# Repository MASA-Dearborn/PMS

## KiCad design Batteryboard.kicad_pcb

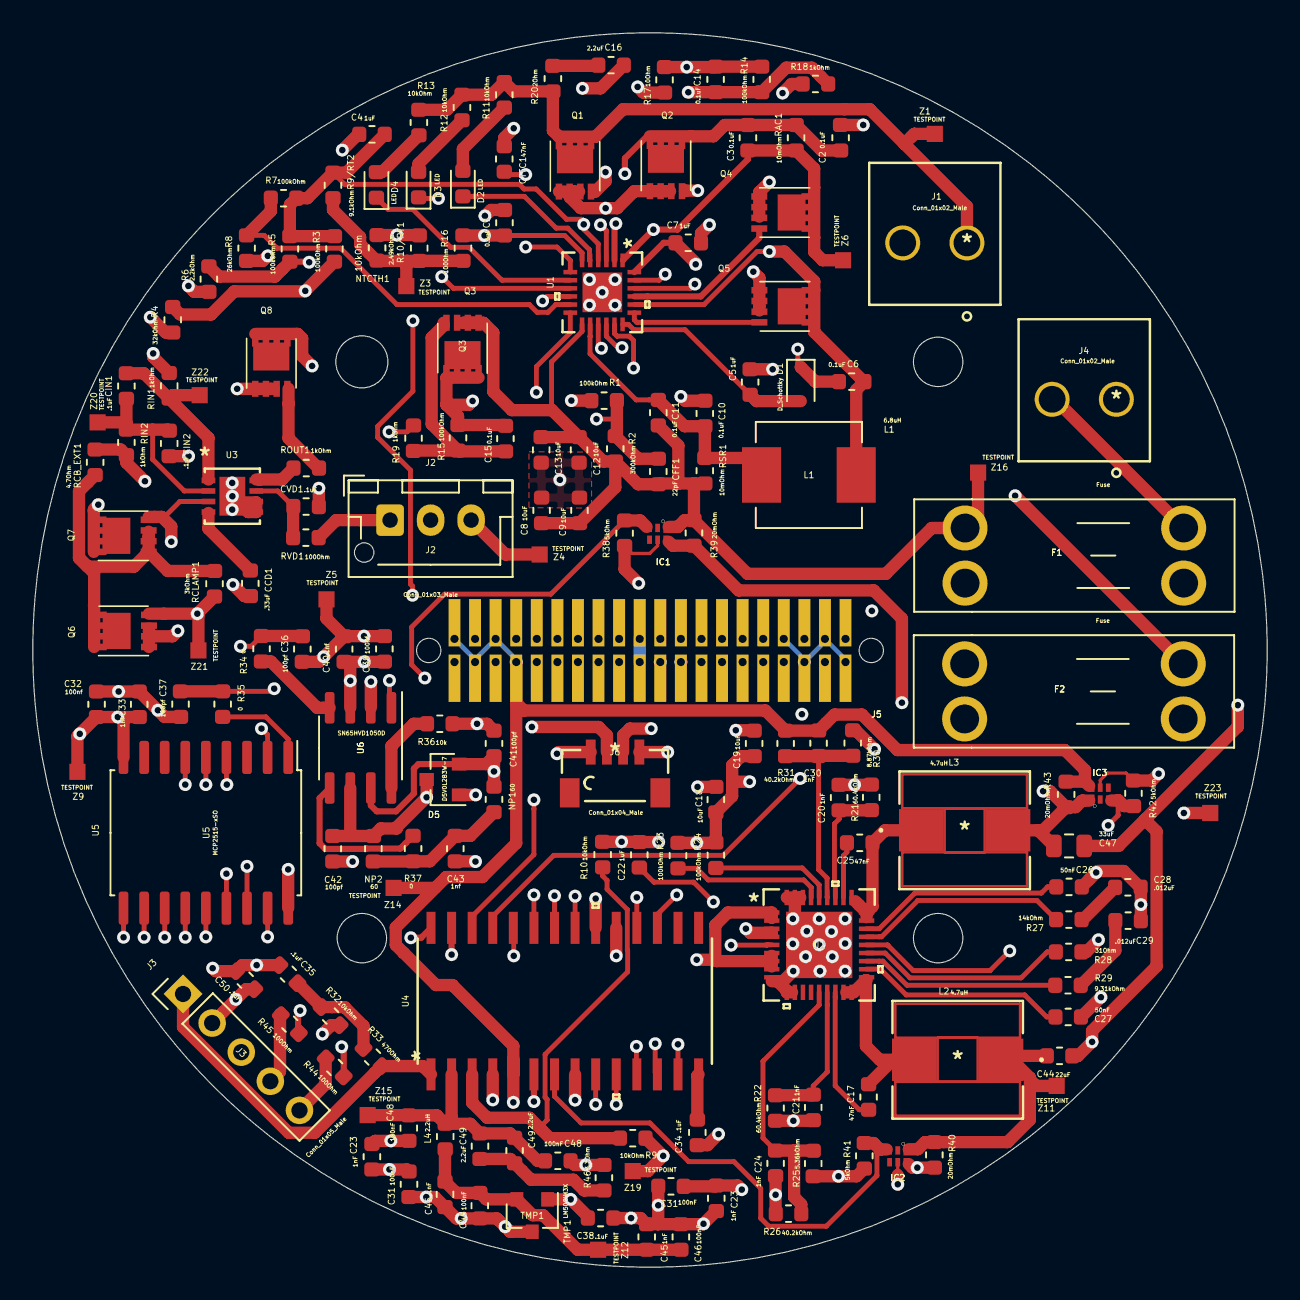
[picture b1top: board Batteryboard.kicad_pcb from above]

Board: 4 copper layers, 76.2 x 76.2 mm, 173 parts (1 on the bottom side), 102 nets.

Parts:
C1, C2, C3, C6, C10, C11, C14, C15: 0.1uF; C_0603_1608Metric
C4, C5, C7, C22: 1uF; C_0603_1608Metric
C8, C9, C12, C13, C18, C19: 10uF; C_0603_1608Metric
C16, C49, C49#2: 2.2uF; C_0603_1608Metric
C17, C25: 47nF; C_0603_1608Metric
C20, C21, C23, C23#2, C24, C30, C45, C45#2: 1nF; C_0603_1608Metric
C26, C27: 50nF; C_0603_1608Metric
C28, C29: .012uF; C_0603_1608Metric
C31, C31#2, C46, C46#2, C48, C48#2: 100nF; C_0603_1608Metric
C32, C40: 100nf; C_0603_1608Metric
C33, C39, C43: 1nf; C_0603_1608Metric
C34, C35, C38, C50: .1uF; C_0603_1608Metric
C36, C37, C41, C42: 100pf; C_0603_1608Metric
C44: 22uF; C_0603_1608Metric
C47: 33uF; C_0805_2012Metric
CCD1: .33uF; C_0603_1608Metric
CFF1: 22pF; C_0603_1608Metric
CIN1, CIN2: .1uF; C_0603_1608Metric
CTTC1: 47nF; C_0603_1608Metric
CVD1: .1uF; C_0603_1608Metric
D1: D_Schottky; D_SOD-323
D2, D3, D4: LED; D_0603_1608Metric
D5: D5V0L2B3W-7; SOT-23
F1, F2: Fuse; Fuseholder_Blade_Mini_Keystone_3557-2
IC1, IC2, IC3: FAN4010IL6X_F113; 6-LEAD_MICROPAK
J1, J4: Conn_01x02_Male; 1-1123723-2
J2: Conn_01x03_Male; JST_XH_B3B-XH-AM_1x03_P2.50mm_Vertical
J3: Conn_01x05_Male; PinHeader_1x05_P2.54mm_Vertical
J5: SC_19-20; bottom_Stack_Connector_2019_2020
J6: Conn_01x04_Male; 1734595-4
L1: 6.8uH; L_Vishay_IHLP-2525
L2, L3: 4.7uH; SRP7030-4R7M
L4: 2.2uH; L_0603_1608Metric
NP1, NP2: 60; R_0603_1608Metric
NTCTH1: 10kOhm; R_0603_1608Metric
Q1, Q2, Q3, Q7: SI7617DN-T1-GE3; SIS862DNT1GE3
Q4, Q5, Q6, Q8: SIS412DN-T1-GE3; SIS862DNT1GE3
R1, R3, R5, R7, R14, R15, R23, R24: 100kOhm; R_0603_1608Metric
R2: 300kOhm; R_0603_1608Metric
R4: 32kOhm; R_0603_1608Metric
R6: 2.2kOhm; R_0603_1608Metric
R8: 26kOhm; R_0603_1608Metric
R9, R10, R11, R12, R13, R32: 10kOhm; R_0603_1608Metric
R9/RT2: 9.1kOhm; R_0603_1608Metric
R10/RT1: 2.49kOhm; R_0603_1608Metric
R16, R44, R45: 100Ohm; R_0603_1608Metric
R17: 10Ohm; R_0603_1608Metric
R18, R19: 1kOhm; R_0603_1608Metric
R20: 2Ohm; R_0603_1608Metric
R21, R22: 60.4kOhm; R_0603_1608Metric
R25: 5.36kOhm; R_0603_1608Metric
R26, R31: 40.2kOhm; R_0603_1608Metric
R27: 14kOhm; R_0603_1608Metric
R28: 31Ohm; R_0603_1608Metric
R29: 9.31kOhm; R_0603_1608Metric
R30: 8.87kOhm; R_0603_1608Metric
R33: 470Ohm; R_0603_1608Metric
R34, R35, R37: 0; R_0603_1608Metric
R36: 10k; R_0603_1608Metric
R38, R41, R42: 5kOhm; R_0603_1608Metric
R39, R40, R43: 20mOhm; R_0603_1608Metric
R46: 3.3Ohm; R_0603_1608Metric
RAC1: 10mOhm; R_0603_1608Metric
RCB_EXT1: 4.7Ohm; R_0603_1608Metric
RCLAMP1: 3kOhm; R_0603_1608Metric
RIN1, RIN2: 1kOhm; R_0603_1608Metric
ROUT1: 1kOhm; R_0603_1608Metric
RSR1: 10mOhm; R_0603_1608Metric
RVD1: 100Ohm; R_0603_1608Metric
R_JUMP1: 0Ohm; R_0603_1608Metric
TMP1: LM50CIM3X; SOT-23
U1: BQ24617RGET
U2: TPS65279DAPR
U3: BQ29200DRBT
U4: PIC18F25K50-I_SO; PIC18F25K50-I&slash_SO
U5: MCP2515-xSO; SOIC-18W_7.5x11.6mm_P1.27mm
U6: SN65HVD1050D; SOIC-8_3.9x4.9mm_P1.27mm
Z1, Z3, Z4, Z5, Z6, Z9, Z11, Z12, Z14, Z15, Z16, Z19, Z20, Z21, Z22, Z23: TESTPOINT

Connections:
3V3: C30.2, C50.1, IC3.6, J3.2, J5.2, J5.3, J5.6, J5.7, R31.2, R43.1, U4.5, Z14.1
3V3CURRENT: IC3.3, R42.1, U4.25
5V0: C23.1, C23#2.1, C24.2, C31.2, C31#2.2, C32.1, C33.2, C38.1, C39.2, C40.1, IC2.6, J5.34, J5.35, J5.38, J5.39, J6.1, R26.2, R32.1, R40.2, TMP1.1, U4.4, U4.20, U5.9, U6.3, Z9.1
5VCURRENT: IC2.3, R41.1, U4.7
ACSET: R3.2, R4.1, U1.16
BTST: C6.2, D1.1, U1.22
CAN_H: C41.2, D5.2, J5.21, J6.3, NP1.1, U6.7
CAN_L: C42.2, D5.3, J5.23, J6.4, NP2.2, U6.6
CS: U4.18, U5.16
FB1: C24.1, R25.2, R26.1, U2.14
FB2: C30.1, R30.2, R31.1, U2.31
INT: U4.23, U5.12
ISET2: R5.2, R6.1, U1.15
LX1: C17.1, L2.2, U2.17, U2.18, U2.19
MCLR: J3.1, R33.2, U4.1
unnamed: C2.1, C3.2, Q2.5, Q2.6, Q2.7, Q2.8, RAC1.2, U1.2
unnamed: C4.1, R3.1, R5.1, R7.1, R9/RT2.2, U1.4, U1.10
unnamed: C7.1, R17.1, U1.24
unnamed: C14.1, Q1.1, Q1.2, Q1.3, Q2.1, Q2.2, Q2.3, R14.1, R17.2
unnamed: C14.2, Q1.4, Q2.4, R14.2, R18.2
unnamed: C15.2, Q3.4, R15.2, R19.1
unnamed: C16.1, R20.2
unnamed: C17.2, U2.16
unnamed: C25.1, L3.1, U2.26, U2.27, U2.28
unnamed: C25.2, U2.29
unnamed: C26.2, U2.25
unnamed: C27.2, U2.20
unnamed: C28.2, R27.1
unnamed: C29.2, R29.1
unnamed: C34.2, U4.14
unnamed: C35.1, R32.2, R33.1
unnamed: C36.1, R34.1, U5.2
unnamed: C37.2, R35.1, U6.1
unnamed: C43.1, NP1.2, NP2.1, R37.2
unnamed: C44.2, IC2.1, L2.1, R40.1, Z11.1
unnamed: C45.2, C45#2.2, C46.2, C46#2.2, L4.1, TMP1.2, Z12.1
unnamed: C47.1, IC3.1, L3.2, R43.2, Z23.1
unnamed: C49.1, C49#2.1, R46.1
unnamed: CCD1.1, U3.4
unnamed: CIN1.1, RIN1.1, U3.1, Z22.1
unnamed: CIN1.2, CIN2.1, RIN2.1, U3.2, Z20.1
unnamed: CTTC1.1, U1.7
unnamed: CVD1.1, RVD1.2, U3.7
unnamed: D2.2, R11.1
unnamed: D3.2, R12.1
unnamed: D4.2, R13.1
unnamed: F1.1, J4.2
unnamed: F2.1, Q8.5, Q8.6, Q8.7, Q8.8
unnamed: J1.1, Q1.5, Q1.6, Q1.7, Q1.8, R11.2, R12.2, R13.2, R20.1, Z1.1
unnamed: J2.2, RCB_EXT1.1, RIN2.2
unnamed: J3.4, R45.2
unnamed: J3.5, R44.1
unnamed: NTCTH1.2, R9/RT2.1, R10/RT1.2, R16.2, Z3.1
unnamed: Q8.4, ROUT1.1
unnamed: R7.2, R8.1, U1.11
unnamed: R9.2, R10.1, U4.3
unnamed: R18.1, U1.3
unnamed: R19.2, U1.23
unnamed: R23.2, U2.33
unnamed: R24.2, U2.32
unnamed: R27.2, U2.24
unnamed: R28.2, U2.22
unnamed: R29.2, U2.21
unnamed: R34.2, U6.4
unnamed: R35.2, U5.1
unnamed: R36.1, U6.8
unnamed: R37.1, U6.5
unnamed: ROUT1.2, U3.8
PG: D4.1, U1.8
PGC: R44.2, U4.27
PGD: R45.1, U4.28
PGND2: C5.2, C8.2, C9.2, C12.2, C13.2, C16.2, C18.1, C19.2, C22.2, C44.1, C47.2, CCD1.2, CIN2.2, CVD1.2, J1.2, J2.3, J4.1, Q5.1, Q5.2, Q5.3, Q7.5, Q7.6, Q7.7, Q7.8, Q8.1, Q8.2, Q8.3, R10.2, R_JUMP1.2, U1.17, U2.9, U2.10, U2.11, U2.34, U2.35, U2.36, U2.37, U3.5, U3.6, U3.9, Z4.1
Q4D: C3.1, C15.1, Q3.5, Q3.6, Q3.7, Q3.8, Q4.5, Q4.6, Q4.7, Q4.8, R15.1, RAC1.1, U1.1, Z6.1
Q4G: Q4.4, U1.21
Q4S: C6.1, L1.1, Q4.1, Q4.2, Q4.3, Q5.5, Q5.6, Q5.7, Q5.8, U1.20
Q5G: Q5.4, U1.19
Q6D: Q6.5, Q6.6, Q6.7, Q6.8, Q7.1, Q7.2, Q7.3, RCB_EXT1.2, RCLAMP1.2
Q6G: Q6.4, Q7.4, RCLAMP1.1, U3.3, Z21.1
Q6S: F2.2, J2.1, Q6.1, Q6.2, Q6.3, RIN1.2, RVD1.1
REGN: C5.1, D1.2, U1.18
RESET: U4.6, U5.17
RLIM1: C21.1, R22.1, U2.15
RLIM2: C20.1, R21.1, U2.30
RX0BF: U4.10, U5.11
RX1BF: U4.9, U5.10
SCK: U4.22, U5.13
SI: U4.24, U5.14
SO: U4.21, U5.15
SRN: C8.1, C9.1, C11.1, C12.1, C13.1, CFF1.1, F1.2, IC1.1, Q3.1, Q3.2, Q3.3, R2.1, R39.2, RSR1.1, U1.13, Z16.1
SRP: C10.1, C11.2, L1.2, RSR1.2, U1.14
STAT1: D2.1, U1.5
STAT2: D3.1, U1.9
TEMP_OUT: C48.2, C48#2.2, C49.2, C49#2.2, L4.2, U4.2, Z15.1
TS: C1.2, R16.1, U1.6, U4.17
TX0RTS: U4.13, U5.4
TX1RTS: U4.12, U5.5
TX2RTS: U4.11, U5.6
V7V: C22.1, U2.5
VBAT: C18.2, C19.1, IC1.6, R9.1, R23.1, R24.1, R39.1, U2.1, U2.2, U2.6, U2.7, U2.8, Z19.1
VBATCURRENT: IC1.3, R38.2, U4.26
VFB: CFF1.2, R1.1, R2.2, U1.12
VSS: C1.1, C2.2, C4.2, C7.2, C10.2, C20.2, C21.2, C23.2, C23#2.2, C26.1, C27.1, C28.1, C29.1, C31.1, C31#2.1, C32.2, C33.1, C34.1, C35.2, C36.2, C37.1, C38.2, C39.1, C40.2, C41.1, C42.1, C43.2, C45.1, C45#2.1, C46.1, C46#2.1, C48.1, C48#2.1, C50.2, CTTC1.2, D5.1, IC1.5, IC2.5, IC3.5, J3.3, J5.1, J5.4, J5.5, J5.19, J5.20, J5.36, J5.37, J5.40, J6.2, NTCTH1.1, R1.2, R4.2, R6.2, R8.2, R10/RT1.1, R21.2, R22.2, R25.1, R28.1, R30.1, R36.2, R38.1, R41.2, R42.2, R46.2, R_JUMP1.1, TMP1.3, U1.25, U2.3, U2.4, U2.23, U4.8, U4.19, U5.18, U6.2, Z5.1

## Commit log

2019-12-23 fixed an error with D1 footprint
2019-12-24 final touches before stefka, fixed a couple small things
2019-12-25 fixed J2, wrong footprint
2019-12-29 fixed a problem on the layout where CTTC1 was connected to traces it shouldnt have been
2019-12-29 needed to use a different cap, cause the value wasnt on digikey
2019-12-29 frick visual studio
2019-12-29 fixed some footprints
2020-02-11 added PMS Rev0

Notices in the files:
parts and their libraries:
Copyright 2016 Accelerated Designs. All rights reserved.
